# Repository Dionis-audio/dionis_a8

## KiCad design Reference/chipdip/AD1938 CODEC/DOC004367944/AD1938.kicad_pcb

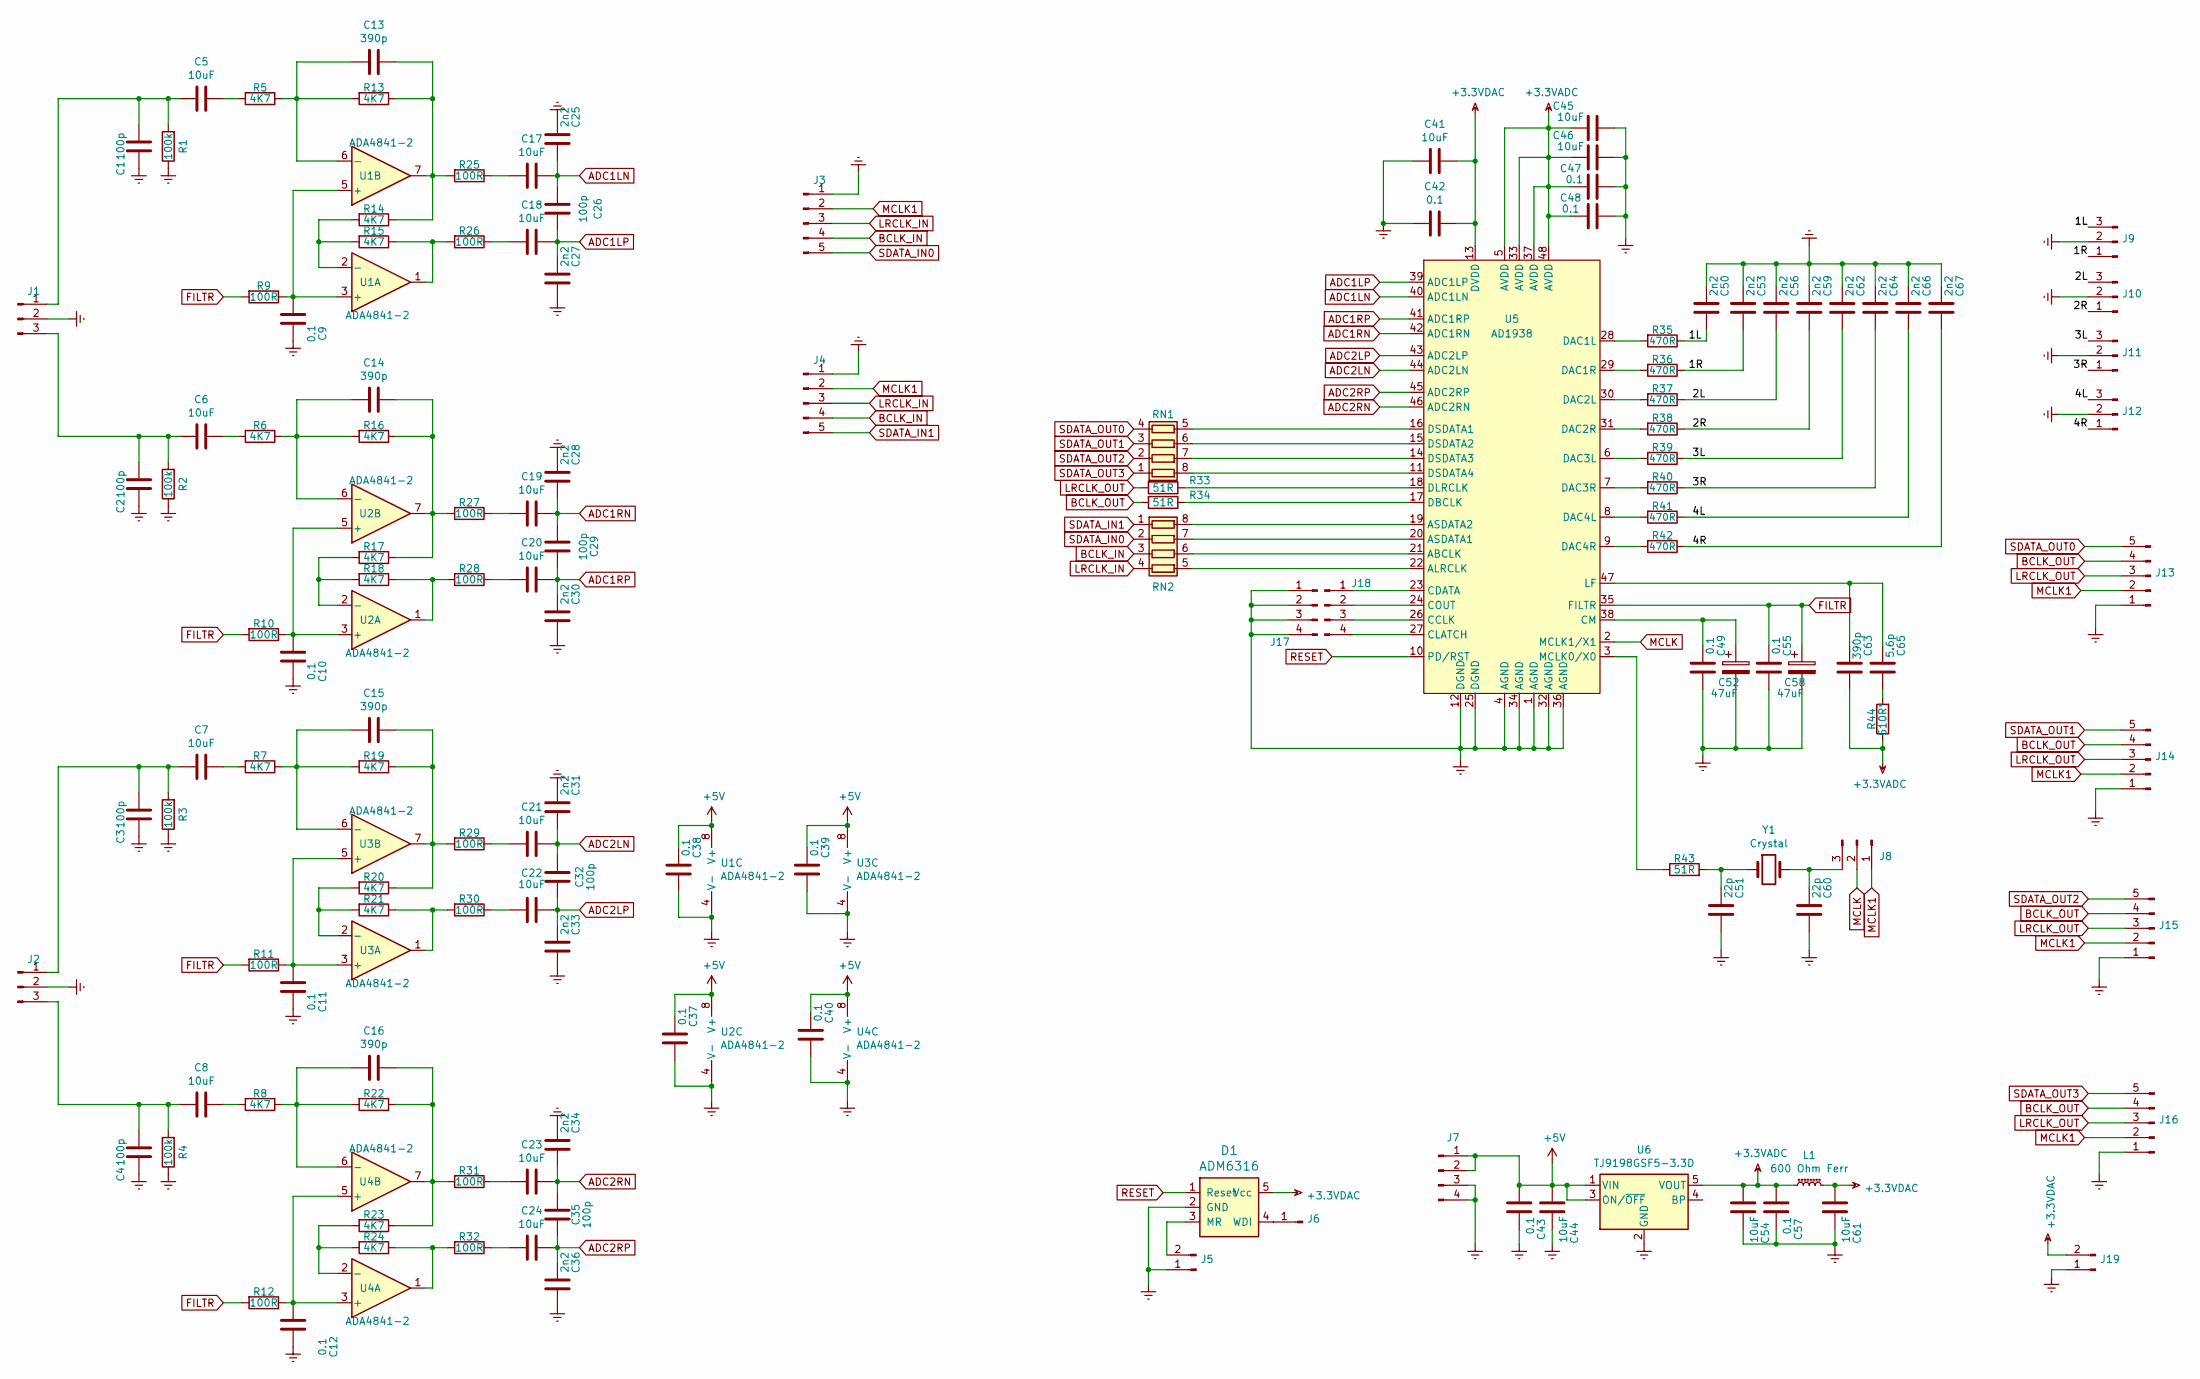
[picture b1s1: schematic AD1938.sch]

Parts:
C1, C26: 100p; C_0201_0603Metric
C2, C3, C4, C29, C32, C35: 100p; C_0603_1608Metric
C5, C6: 10uF; C_0603
C7, C8, C18, C19, C20, C21, C22, C23, C24, C41, C44, C45, C46, C54, C61: 10uF; C_0603_1608Metric
C9, C10, C11, C12, C37, C38, C39, C40, C42, C43, C47, C48, C49, C55, C57: 0.1; C_0603_1608Metric
C13: 390p; C_0201_0603Metric
C14, C15, C16, C63: 390p; C_0603_1608Metric
C17: 10uF; C_0201_0603Metric
C25: 2n2; C_0201_0603Metric
C27, C28, C30, C31, C33, C34, C36, C50, C53, C56, C59, C62, C64, C66, C67: 2n2; C_0603_1608Metric
C51, C60: 22p; C_0603_1608Metric
C52, C58: 47uF; TantalC_SizeB_EIA-3528_Reflow
C65: 5.6p; C_0603_1608Metric
D1: ADM6316; SOT-23-5
J1, J2, J9, J10, J11, J12: Conn_01x03_Male; PinHeader_1x03_P2.54mm_Vertical
J3, J4, J13, J14, J15, J16: Conn_01x05_Male; Pin_Header_Straight_1x05
J5: Conn_01x02_Male; PinHeader_1x02_P2.54mm_Vertical
J6: Conn_01x01_Male; PinHeader_1x01_P2.54mm_Vertical
J7: Conn_01x04_Male; Pin_Header_Straight_2x02
J8: Conn_01x03_Male; Pin_Header_Straight_1x03
J17, J18: Conn_01x04_Male; Pin_Header_Straight_1x04
J19: Conn_01x02_Male; Pin_Header_Straight_1x02
L1: 600 Ohm Ferr; C_0201_0603Metric
R1, R2, R3, R4: 100k; R_0603_1608Metric
R5, R6, R7, R8, R13, R14, R15, R16, R17, R18, R19, R20, R21, R22, R23, R24: 4K7; R_0603_1608Metric
R9, R10, R11, R12, R25, R26, R27, R28, R29, R30, R31, R32: 100R; R_0603_1608Metric
R33, R34, R43: 51R; R_0603_1608Metric
R35, R36, R37, R38, R39, R40, R41, R42: 470R; R_0603_1608Metric
R44: 510R*; R_0603_1608Metric
RN1, RN2: R_Pack04; R_Array_Convex_4x0603
U1, U2, U3, U4: ADA4841-2; MSOP-8_3x3mm_P0.65mm
U5: AD1938; LQFP-48_7x7mm_Pitch0.5mm
U6: TJ9198GSF5-3.3D; SOT-23-5
Y1: Crystal; Crystal_HC49-4H_Vertical

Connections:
+3.3VADC: C45.1, C46.1, C47.1, C48.1, C54.1, C57.1, C63.2, L1.1, R44.1, U5.5 (AVDD), U5.33 (AVDD), U5.37 (AVDD), U5.48 (AVDD), U6.5 (VOUT)
+3.3VDAC: C41.2, C42.2, C61.1, D1.5 (Vcc), J19.2, L1.2, U5.13 (DVDD)
+5V: C37.1, C38.1, C39.1, C40.1, C43.1, C44.1, J7.1, J7.2, U1.8 (V+), U2.8 (V+), U3.8 (V+), U4.8 (V+), U6.1 (VIN), U6.3 (ON/~OFF~)
/1L: C50.2, J9.3, R35.1
/1R: C53.2, J9.1, R36.1
/2L: C56.2, J10.3, R37.1
/2R: C59.2, J10.1, R38.1
/3L: C62.2, J11.3, R39.1
/3R: C64.2, J11.1, R40.1
/4L: C66.2, J12.3, R41.1
/4R: C67.2, J12.1, R42.1
ADC1LN: C17.2, C25.2, C26.1, U5.40 (ADC1LN)
ADC1LP: C18.2, C26.2, C27.1, U5.39 (ADC1LP)
ADC1RN: C19.2, C28.2, C29.1, U5.42 (ADC1RN)
ADC1RP: C20.2, C29.2, C30.1, U5.41 (ADC1RP)
ADC2LN: C21.2, C31.2, C32.1, U5.44 (ADC2LN)
ADC2LP: C22.2, C32.2, C33.1, U5.43 (ADC2LP)
ADC2RN: C23.2, C34.2, C35.1, U5.46 (ADC2RN)
ADC2RP: C24.2, C35.2, C36.1, U5.45 (ADC2RP)
BCLK_IN: J3.4, J4.4, RN2.3 (R3.1)
BCLK_OUT: J13.4, J14.4, J15.4, J16.4, R34.2; also elsewhere on the board
Earth: C1.2, C2.2, C3.2, C4.2, C9.2, C10.2, C11.2, C12.2, C25.1, C27.2, C28.1, C30.2, C31.1, C33.2, C34.1, C36.2, C37.2, C38.2, C39.2, C40.2, C41.1, C42.1, C43.2, C44.2, C45.2, C46.2, C47.2, C48.2, C49.2, C50.1, C51.2, C52.2, C53.1, C54.2, C55.2, C56.1, C57.2, C58.2, C59.1, C60.2, C61.2, C62.1, C64.1, C66.1, C67.1, D1.2 (GND), J1.2, J2.2, J3.1, J4.1, J5.1, J7.3, J7.4, J9.2, J10.2, J11.2, J12.2, J13.1, J14.1, J15.1, J16.1, J17.1, J17.2, J17.3, J17.4, J19.1, R1.1, R2.1, R3.1, R4.1, U1.4 (V-), U2.4 (V-), U3.4 (V-), U4.4 (V-), U5.1 (AGND), U5.4 (AGND), U5.12 (DGND), U5.25 (DGND), U5.32 (AGND), U5.34 (AGND), U5.36 (AGND), U6.2 (GND); also elsewhere on the board
FILTR: C55.1, C58.1, R9.2, R10.2, R11.2, R12.2, U5.35 (FILTR)
LRCLK_IN: J3.3, J4.3, RN2.4 (R4.1)
LRCLK_OUT: J13.3, J14.3, J15.3, J16.3, R33.2; also elsewhere on the board
MCLK: J8.2, U5.2 (MCLK1/X1)
MCLK1: J3.2, J4.2, J8.1, J13.2, J14.2, J15.2, J16.2; also elsewhere on the board
unnamed: C1.1, C5.1, J1.1, R1.2
unnamed: C2.1, C6.1, J1.3, R2.2
unnamed: C3.1, C7.1, J2.1, R3.2
unnamed: C4.1, C8.1, J2.3, R4.2
unnamed: C5.2, R5.2
unnamed: C6.2, R6.2
unnamed: C7.2, R7.2
unnamed: C8.2, R8.2
unnamed: C9.1, R9.1, U1.3 (+), U1.5 (+)
unnamed: C10.1, R10.1, U2.3 (+), U2.5 (+)
unnamed: C11.1, R11.1, U3.3 (+), U3.5 (+)
unnamed: C12.1, R12.1, U4.3 (+), U4.5 (+)
unnamed: C13.1, R5.1, R13.2, U1.6 (-)
unnamed: C13.2, R13.1, R14.1, R25.2, U1.7
unnamed: C14.1, R6.1, R16.2, U2.6 (-)
unnamed: C14.2, R16.1, R17.1, R27.2, U2.7
unnamed: C15.1, R7.1, R19.2, U3.6 (-)
unnamed: C15.2, R19.1, R20.1, R29.2, U3.7
unnamed: C16.1, R8.1, R22.2, U4.6 (-)
unnamed: C16.2, R22.1, R23.1, R31.2, U4.7
unnamed: C17.1, R25.1
unnamed: C18.1, R26.1
unnamed: C19.1, R27.1
unnamed: C20.1, R28.1
unnamed: C21.1, R29.1
unnamed: C22.1, R30.1
unnamed: C23.1, R31.1
unnamed: C24.1, R32.1
unnamed: C49.1, C52.1, U5.38 (CM)
unnamed: C51.1, R43.2, Y1.1
unnamed: C60.1, J8.3, Y1.2
unnamed: C63.1, C65.1, U5.47 (LF)
unnamed: C65.2, R44.2
unnamed: D1.3 (MR), J5.2
unnamed: D1.4 (WDI), J6.1
unnamed: J18.1, U5.23 (CDATA)
unnamed: J18.2, U5.24 (COUT)
unnamed: J18.3, U5.26 (CCLK)
unnamed: J18.4, U5.27 (CLATCH)
unnamed: R14.2, R15.2, U1.2 (-)
unnamed: R15.1, R26.2, U1.1
unnamed: R17.2, R18.2, U2.2 (-)
unnamed: R18.1, R28.2, U2.1
unnamed: R20.2, R21.2, U3.2 (-)
unnamed: R21.1, R30.2, U3.1
unnamed: R23.2, R24.2, U4.2 (-)
unnamed: R24.1, R32.2, U4.1
unnamed: R33.1, U5.18 (DLRCLK)
unnamed: R34.1, U5.17 (DBCLK)
unnamed: R35.2, U5.28 (DAC1L)
unnamed: R36.2, U5.29 (DAC1R)
unnamed: R37.2, U5.30 (DAC2L)
unnamed: R38.2, U5.31 (DAC2R)
unnamed: R39.2, U5.6 (DAC3L)
unnamed: R40.2, U5.7 (DAC3R)
unnamed: R41.2, U5.8 (DAC4L)
unnamed: R42.2, U5.9 (DAC4R)
unnamed: R43.1, U5.3 (MCLK0/X0)
unnamed: RN1.5 (R4.2), U5.16 (DSDATA1)
unnamed: RN1.6 (R3.2), U5.15 (DSDATA2)
unnamed: RN1.7 (R2.2), U5.14 (DSDATA3)
unnamed: RN1.8 (R1.2), U5.11 (DSDATA4)
unnamed: RN2.5 (R4.2), U5.22 (ALRCLK)
unnamed: RN2.6 (R3.2), U5.21 (ABCLK)
unnamed: RN2.7 (R2.2), U5.20 (ASDATA1)
unnamed: RN2.8 (R1.2), U5.19 (ASDATA2)
RESET: D1.1 (Reset), U5.10 (PD/RST)
SDATA_IN0: J3.5, RN2.2 (R2.1)
SDATA_IN1: J4.5, RN2.1 (R1.1)
SDATA_OUT0: J13.5, RN1.4 (R4.1); also elsewhere on the board
SDATA_OUT1: J14.5, RN1.3 (R3.1)
SDATA_OUT2: J15.5, RN1.2 (R2.1)
SDATA_OUT3: J16.5, RN1.1 (R1.1)

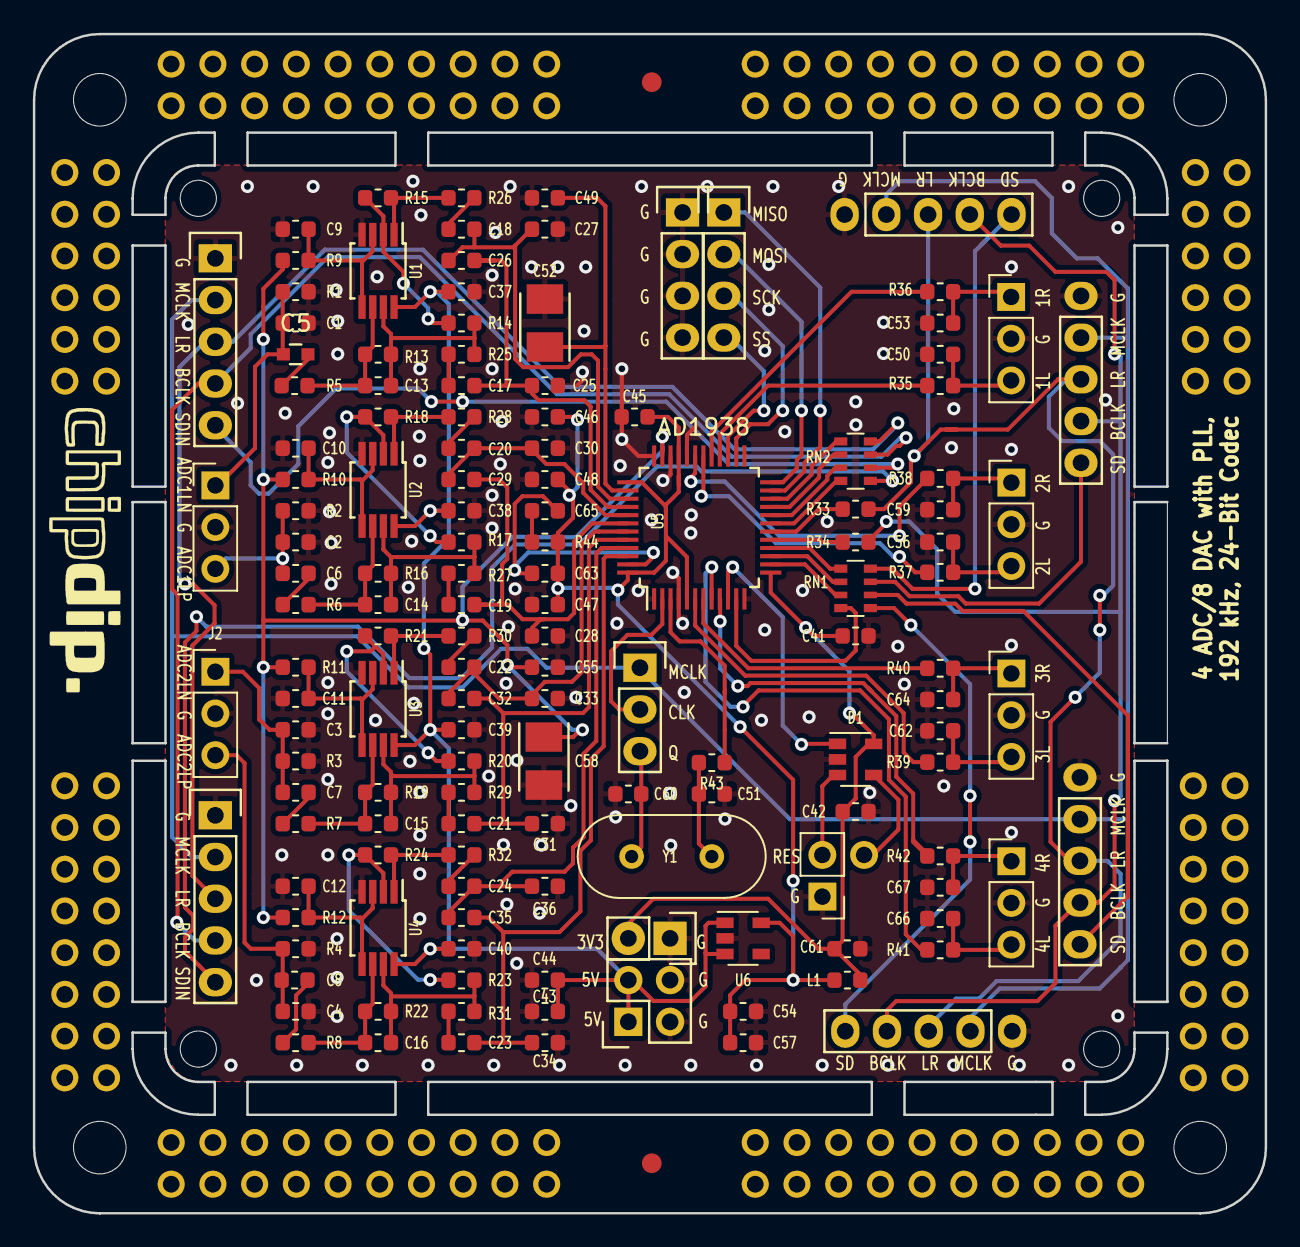
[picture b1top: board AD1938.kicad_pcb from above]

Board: 2 copper layers, 75.0 x 71.8 mm, 161 parts (0 on the bottom side), 100 nets.

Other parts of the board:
J13#2, J13#3, J13#4, J13#5, J13#6, J13#12, J13#13, J13#14, J13#15, J13#16, J13#17, J13#18, J13#19, J13#20, J13#21: MODULE_HEADER; 1x8_BIG
J13#7: Conn_01x05_Male; Pin_Header_Straight_1x05
J13#8, J13#9, J13#10, J13#11: MODULE_HEADER; 1x6_BIG

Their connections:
BCLK_OUT: J13#7.4; also elsewhere on the board
Earth: J13#7.1; also elsewhere on the board
LRCLK_OUT: J13#7.3; also elsewhere on the board
MCLK1: J13#7.2; also elsewhere on the board
SDATA_OUT0: J13#7.5; also elsewhere on the board

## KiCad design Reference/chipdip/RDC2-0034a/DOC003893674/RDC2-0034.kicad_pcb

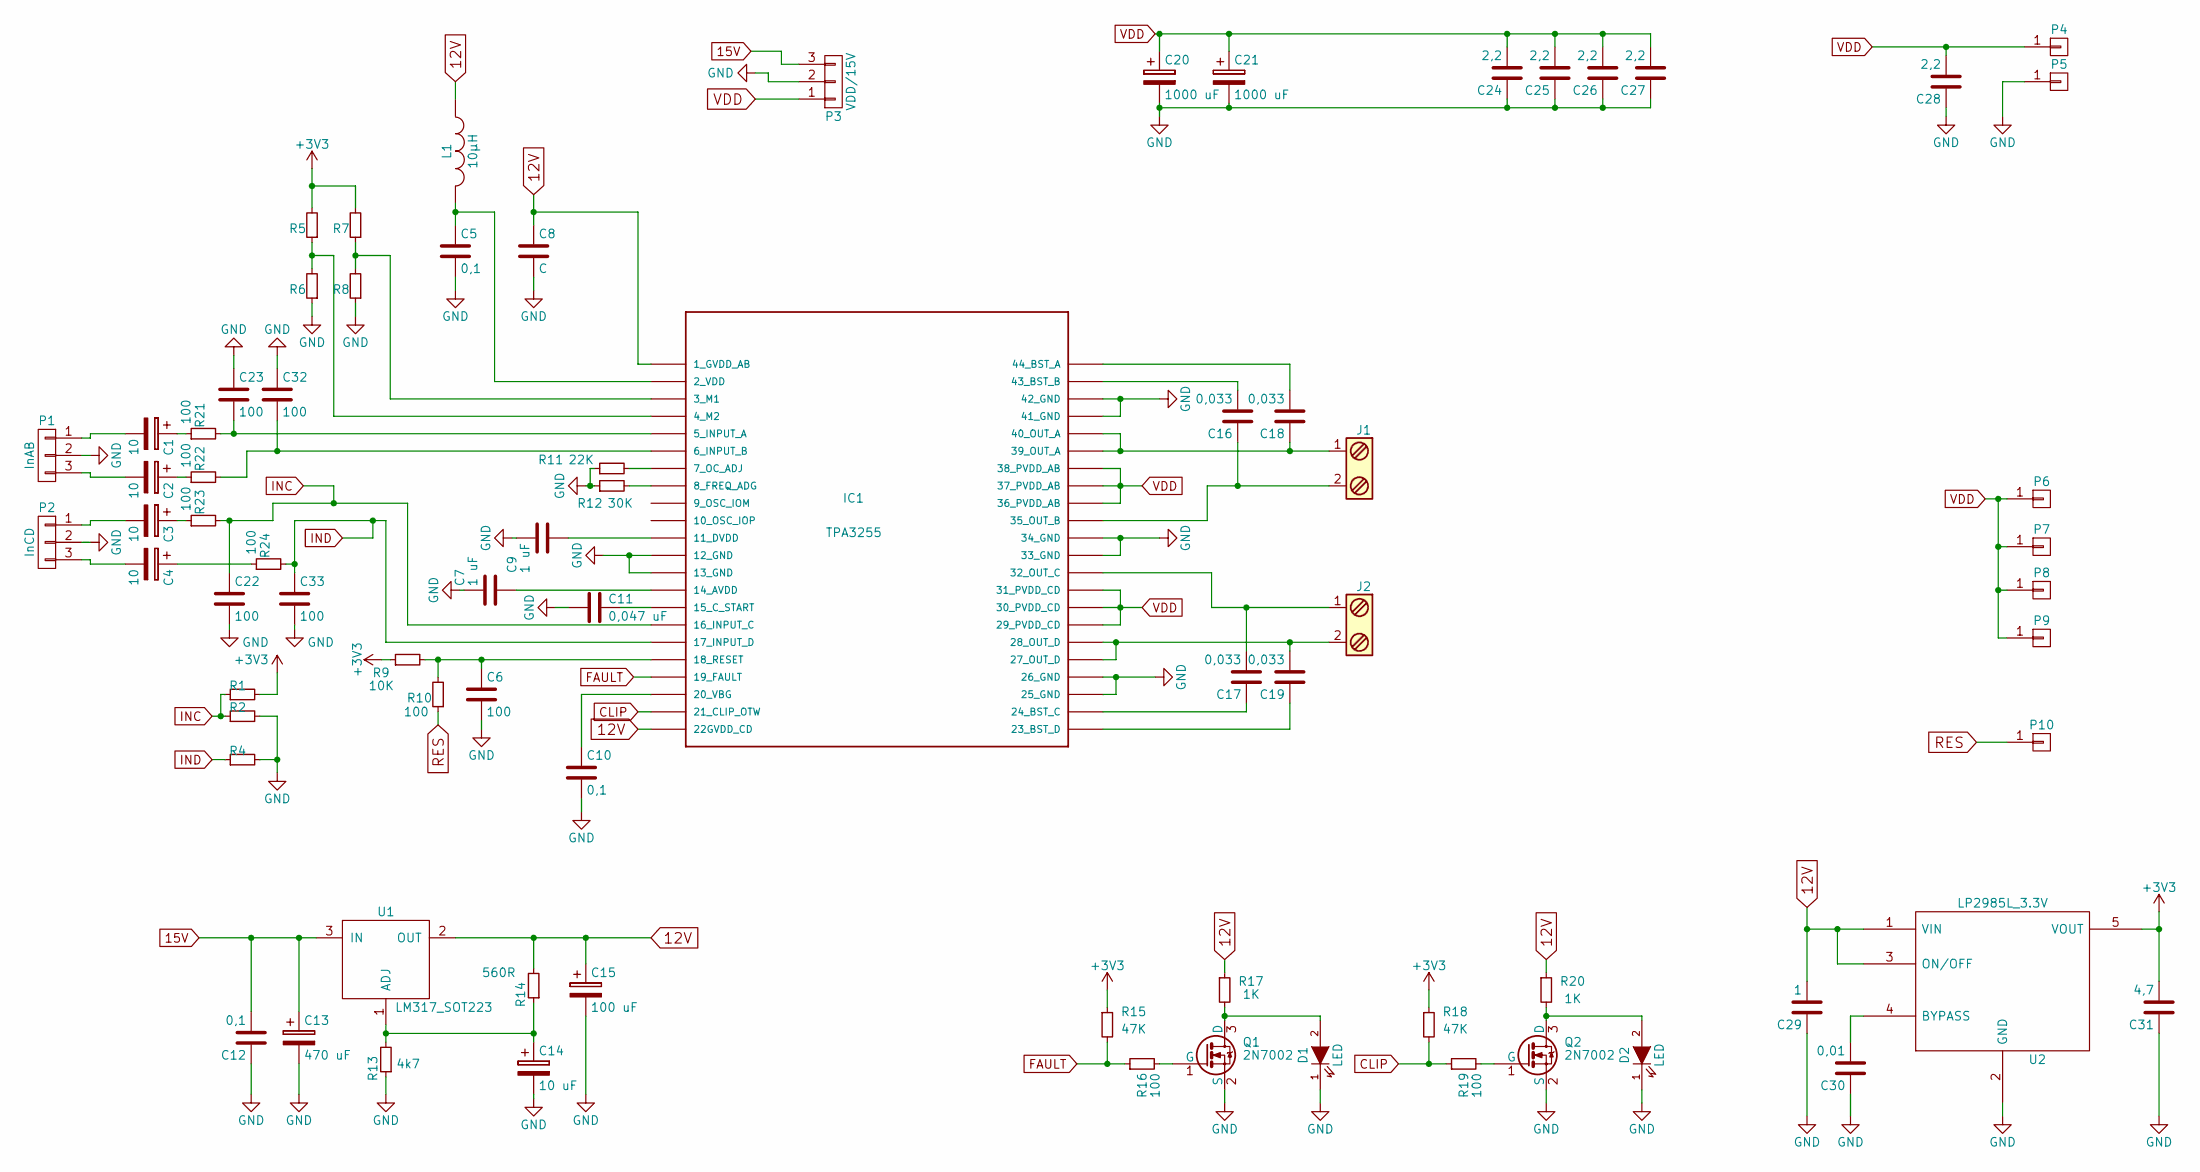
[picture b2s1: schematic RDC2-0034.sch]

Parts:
C1, C2, C3, C4: 10; TantalC_SizeA_EIA-3216_Reflow
C5, C10, C12: 0,1; C_0603
C6, C22, C23, C32, C33: 100; C_0603
C7, C9: 1 uF; C_0603
C8: C; C_0603
C11: 0,047 uF; C_0603
C13: 470 uF; C_Radial_D10_L13_P5
C14: 10 uF; C_Radial_D5_L11_P2
C15: 100 uF; C_Radial_D8_L11.5_P3.5
C16, C17, C18, C19: 0,033; C_0603
C20, C21: 1000 uF; C_Radial_D16_L25_P7.5
C24, C25, C26, C27, C28: 2,2; C_1210
C29: 1; C_0603
C30: 0,01; C_0603
C31: 4,7; C_0603
D1, D2: LED; LED_0603
IC1: TPA3255; TSSOP-44
J1, J2: Screw_Terminal_1x02; Clem_2Pos_P5
L1: 10μH; Neosid_Inductor_SM0603CG
P1: InAB; Pin_Header_Straight_1x03_mm
P2: InCD; Pin_Header_Straight_1x03_mm
P3: VDD/15V; Pin_Header_Straight_1x03_mm
P4, P5: CONN_01X01; Measurement_Point_Round-TH_Big
P6, P7, P8, P9, P10: CONN_01X01; Measurement_Point_Round-TH_Small
Q1, Q2: 2N7002; SOT-23
R1, R2, R4, R5, R6, R7, R8: R; R_0603
R9: 10K; R_0603
R10, R16, R19, R21, R22, R23, R24: 100; R_0603
R11: 22K; R_0603
R12: 30K; R_0603
R13: 4k7; R_0603
R14: 560R; R_0603
R15, R18: 47K; R_0603
R17, R20: 1K; R_0603
U1: LM317_SOT223; SOT-223
U2: LP2985L_3.3V; SOT-23-5

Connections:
12V: C8.1, C15.1, C29.2, IC1.1 (1_GVDD_AB), IC1.22 (22GVDD_CD), L1.1, R14.2, R17.1, R20.1, U1.2 (OUT), U2.1 (VIN), U2.3 (ON/OFF)
15V: C12.2, C13.1, P3.3, U1.3 (IN)
+3V3: C31.2, R1.2, R5.2, R7.2, R9.1, R15.1, R18.1, U2.5 (VOUT)
CLIP: IC1.21 (21_CLIP_OTW), R18.2, R19.1
FAULT: IC1.19 (19_FAULT), R15.2, R16.1
GND: C5.2, C6.2, C7.2, C8.2, C9.2, C10.2, C11.2, C12.1, C13.2, C14.2, C15.2, C20.2, C21.2, C22.2, C23.1, C24.1, C25.1, C26.1, C27.1, C28.1, C29.1, C30.1, C31.1, C32.1, C33.2, D1.1 (K), D2.1 (K), IC1.12 (12_GND), IC1.13 (13_GND), IC1.25 (25_GND), IC1.26 (26_GND), IC1.33 (33_GND), IC1.34 (34_GND), IC1.41 (41_GND), IC1.42 (42_GND), P1.2, P2.2, P3.2, P5.1, Q1.2 (S), Q2.2 (S), R2.2, R4.2, R6.1, R8.1, R11.1, R12.1, R13.1, U2.2 (GND)
INC: C22.1, IC1.16 (16_INPUT_C), R1.1, R2.1, R23.2
IND: C33.1, IC1.17 (17_INPUT_D), R4.1, R24.2
unnamed: C1.1, R21.1
unnamed: C1.2, P1.1
unnamed: C2.1, R22.1
unnamed: C2.2, P1.3
unnamed: C3.1, R23.1
unnamed: C3.2, P2.1
unnamed: C4.1, R24.1
unnamed: C4.2, P2.3
unnamed: C5.1, IC1.2 (2_VDD), L1.2
unnamed: C6.1, IC1.18 (18_RESET), R9.2, R10.2
unnamed: C7.1, IC1.14 (14_AVDD)
unnamed: C9.1, IC1.11 (11_DVDD)
unnamed: C10.1, IC1.20 (20_VBG)
unnamed: C11.1, IC1.15 (15_C_START)
unnamed: C14.1, R13.2, R14.1, U1.1 (ADJ)
unnamed: C16.1, IC1.35 (35_OUT_B), J1.2
unnamed: C16.2, IC1.43 (43_BST_B)
unnamed: C17.1, IC1.24 (24_BST_C)
unnamed: C17.2, IC1.32 (32_OUT_C), J2.1
unnamed: C18.1, IC1.39 (39_OUT_A), IC1.40 (40_OUT_A), J1.1
unnamed: C18.2, IC1.44 (44_BST_A)
unnamed: C19.1, IC1.23 (23_BST_D)
unnamed: C19.2, IC1.27 (27_OUT_D), IC1.28 (28_OUT_D), J2.2
unnamed: C23.2, IC1.5 (5_INPUT_A), R21.2
unnamed: C30.2, U2.4 (BYPASS)
unnamed: C32.2, IC1.6 (6_INPUT_B), R22.2
unnamed: D1.2 (A), Q1.3 (D), R17.2
unnamed: D2.2 (A), Q2.3 (D), R20.2
unnamed: IC1.3 (3_M1), R7.1, R8.2
unnamed: IC1.4 (4_M2), R5.1, R6.2
unnamed: IC1.7 (7_OC_ADJ), R11.2
unnamed: IC1.8 (8_FREQ_ADG), R12.2
unnamed: Q1.1 (G), R16.2
unnamed: Q2.1 (G), R19.2
RES: P10.1, R10.1
VDD: C20.1, C21.1, C24.2, C25.2, C26.2, C27.2, C28.2, IC1.29 (29_PVDD_CD), IC1.30 (30_PVDD_CD), IC1.31 (31_PVDD_CD), IC1.36 (36_PVDD_AB), IC1.37 (37_PVDD_AB), IC1.38 (38_PVDD_AB), P3.1, P4.1, P6.1, P7.1, P8.1, P9.1

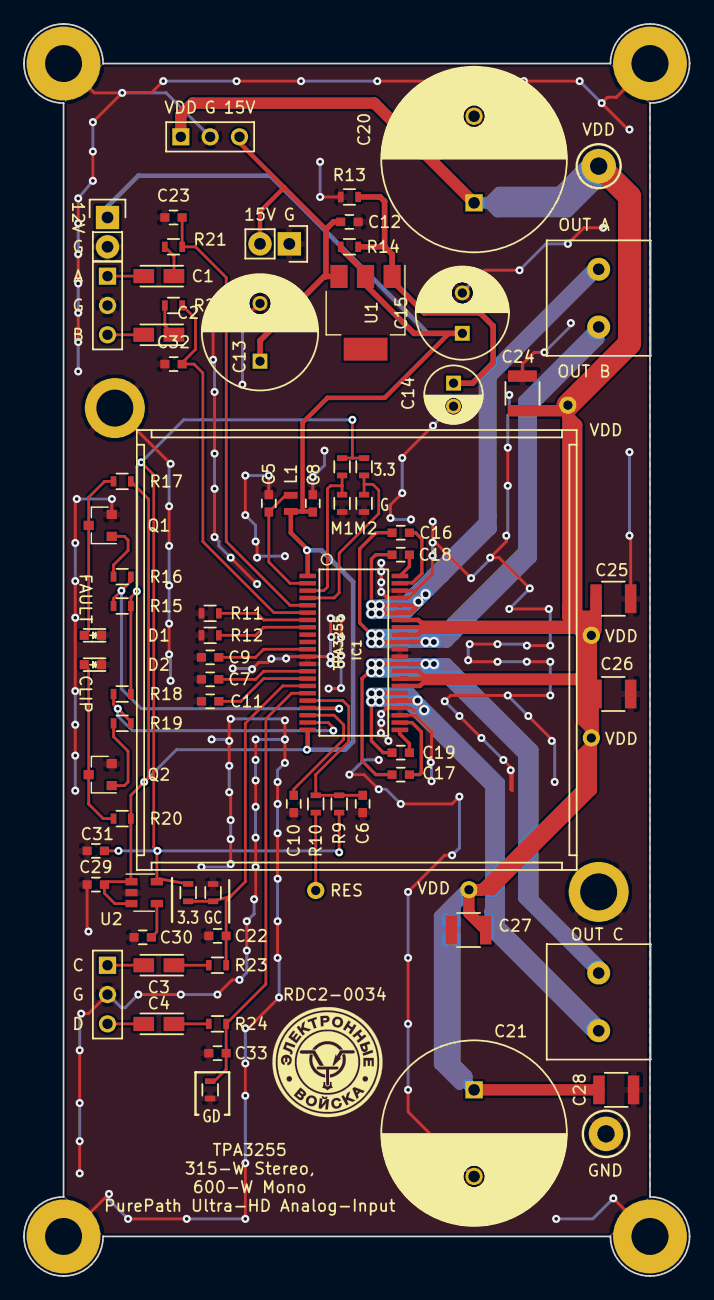
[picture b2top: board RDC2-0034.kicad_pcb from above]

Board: 2 copper layers, 57.7 x 108.5 mm, 76 parts (0 on the bottom side), 44 nets.

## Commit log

2020-05-12 init commit
